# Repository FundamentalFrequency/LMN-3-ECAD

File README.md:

# LMN-3-ECAD

This repository contains the [KiCad 6](https://www.kicad.org/) project files for the LMN-3 PCB.

If you would like to support the project, please consider becoming a [sponsor](https://github.com/sponsors/stonepreston).

## Bill of Materials
| Description                | Model                            | Quantity | URL                                                                                            |
|----------------------------|----------------------------------|----------|------------------------------------------------------------------------------------------------|
| Diode                      | 1N4148                           | 49       | https://www.amazon.com/McIgIcM-1n4148-switching-Standard-Through/dp/B06XB1R2NK                 |
| Rotary Encoder             | EC11                             | 4        | https://www.amazon.com/WayinTop-Encoder-Potentiometer-Electronics-Projects/dp/B08728K3YB?psc=1 |
| Switch                     | 5 pin mechanical keyboard switch | 45       |                                                                                                |
| Joystick                   | COM-09032                        | 1        | https://www.sparkfun.com/products/9032                                                         |                                                                                        |
| Microcontroller            | Teensy 4.1                       | 1        | https://www.pjrc.com/store/teensy41.html                                                       |
| Arduino Header Strip                    |                            | 2      | https://www.amazon.com/gp/product/B07PKKY8BX?psc=1                 |

## Gerbers
Gerber files are available [here](https://github.com/FundamentalFrequency/LMN-3-ECAD/releases) if you would like to have a board house manufacture the PCB. 

## Thanks
This project would not be possible without the following free and open source projects:
- [KiCad](https://www.kicad.org/)
- [Keyswitch Kicad Library](https://github.com/perigoso/keyswitch-kicad-library)

### Sources for Footprints, Symbols, 3-D Models, and Other Resources
#### Encoders (Alps EC11E09244AQ)
- [Product Page](https://www.mouser.com/ProductDetail/Alps-Alpine/EC11E09244AQ?qs=fMKjfF2mFohVUA4%2Ftyw7NQ%3D%3D)
- [Datasheet and Mechanical Drawing](https://tech.alpsalpine.com/prod/e/html/encoder/incremental/ec11/ec11e09244aq.html)
- [3-D Model](https://www.snapeda.com/parts/EC11E09244AQ/ALPS/view-part/?welcome=home&t=EC11E)

#### Teensy 4.1
- [Product Page](https://www.pjrc.com/store/teensy41.html)
- [3-D Model](https://www.snapeda.com/parts/DEV-16771/SparkFun%20Electronics/view-part/?t=teensy)

#### Thumbstick (SparkFun COM-09032)
- [Product Page](https://www.digikey.com/en/products/detail/sparkfun-electronics/COM-09032/6823623)
- [Datasheet](https://media.digikey.com/pdf/Data%20Sheets/Sparkfun%20PDFs/COM-09032_Web.pdf)
- [3-D Model](https://www.snapeda.com/parts/COM-09032/SparkFun%20Electronics/view-part/?t=joystick)
- [Eagle Library](https://github.com/sparkfun/SparkFun-Eagle-Libraries)

#### Keyboard Switches (Keyswitch Kicad Library)
- [Footprints, Symbols, and 3-D Models](https://github.com/perigoso/keyswitch-kicad-library)

## License
Licensed under the  [CC-by-SA 4.0](https://creativecommons.org/licenses/by-sa/4.0/) license.

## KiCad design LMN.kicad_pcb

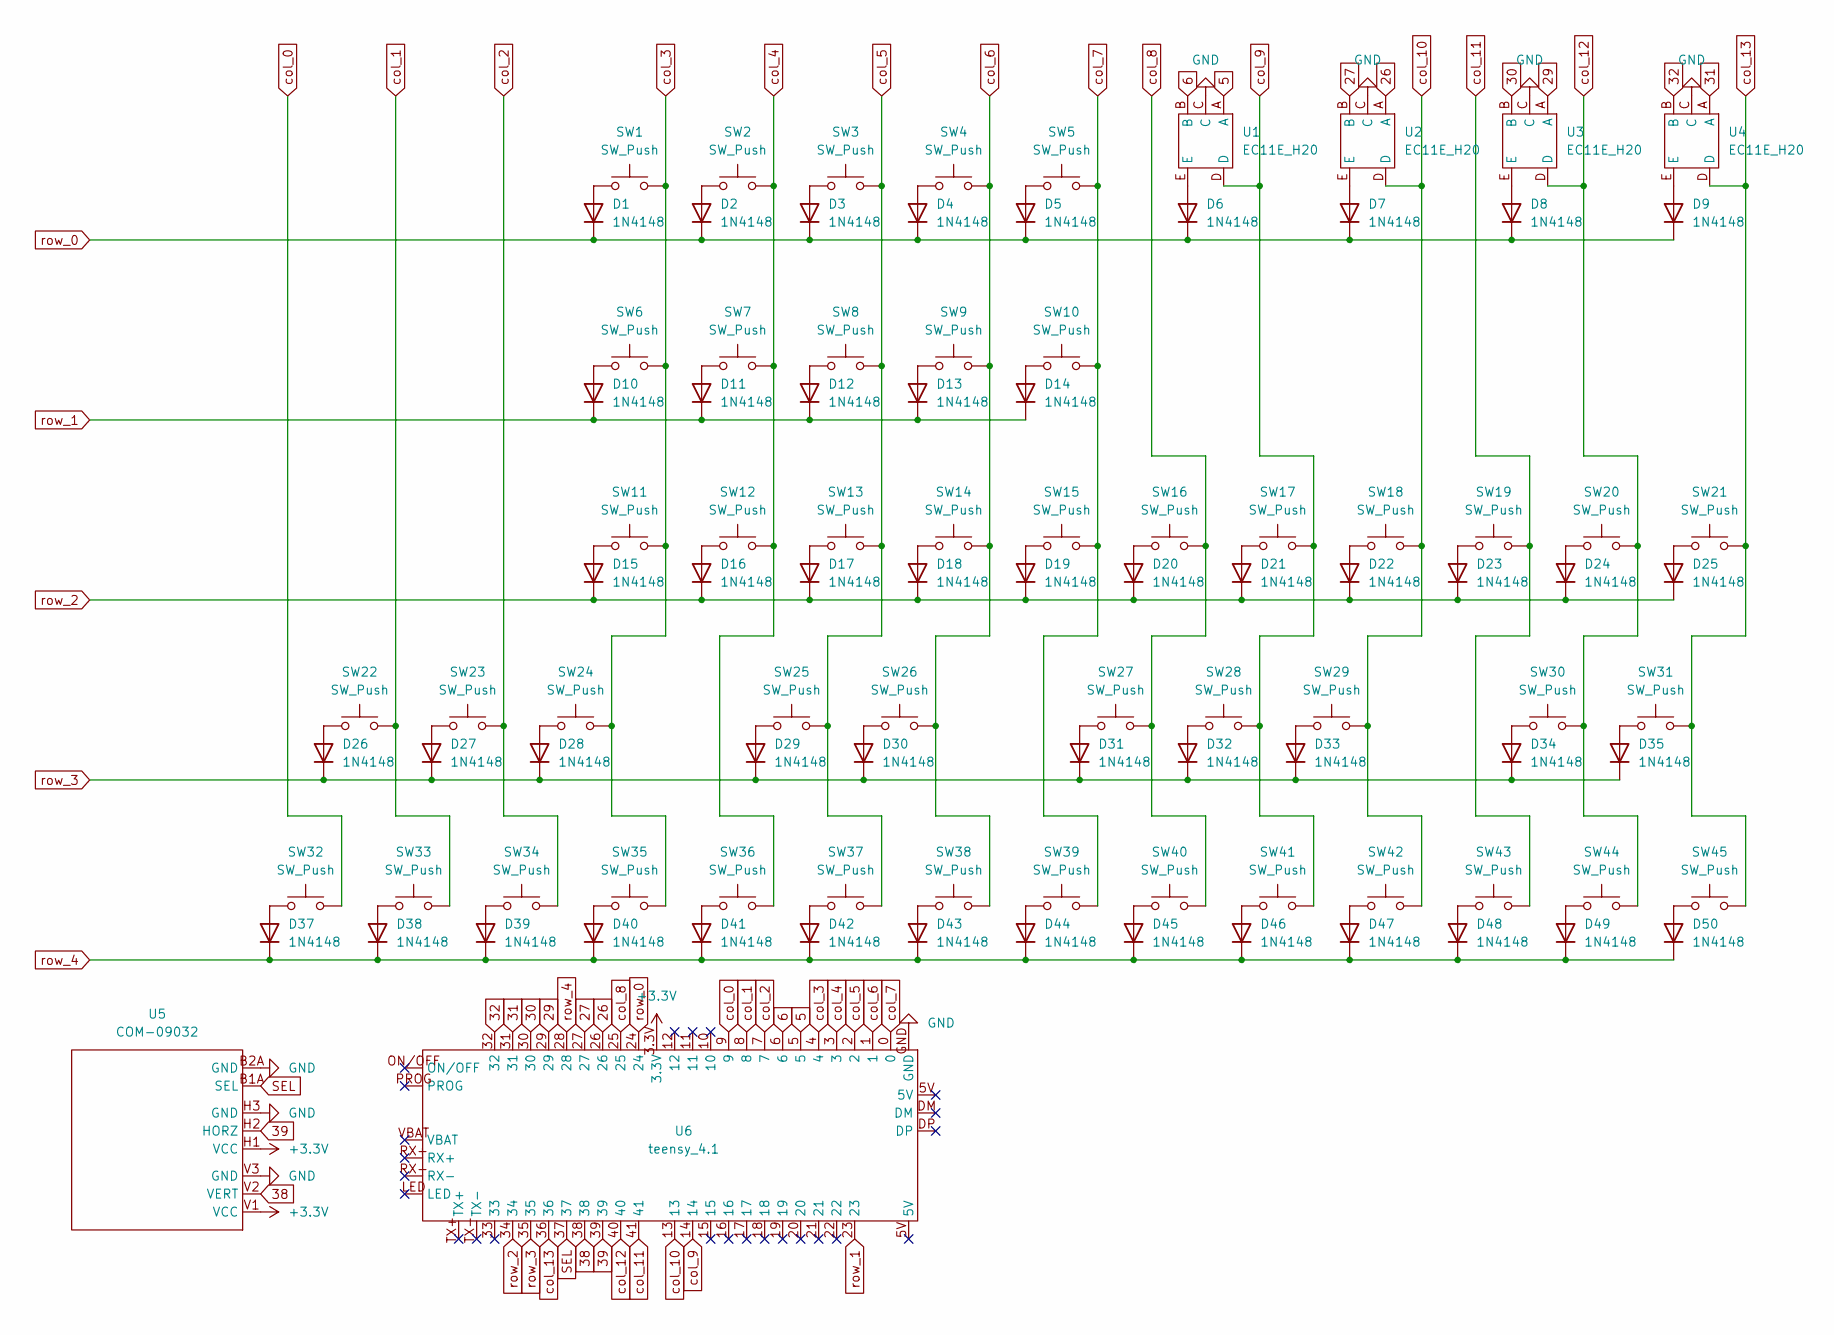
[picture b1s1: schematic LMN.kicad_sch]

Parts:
D1, D2, D3, D4, D5, D6, D7, D8, D9, D10, D11, D12, D13, D14, D15, D16, D17, D18, D19, D20, D21, D22, D23, D24, D25, D26, D27, D28, D29, D30, D31, D32, D33, D34, D35, D37, D38, D39, D40, D41, D42, D43, D44, D45, D46, D47, D48, D49, D50: 1N4148; D_DO-35_SOD27_P7.62mm_Horizontal
SW1, SW2, SW3, SW4, SW5, SW6, SW7, SW8, SW9, SW10, SW11, SW12, SW13, SW14, SW15, SW16, SW17, SW18, SW19, SW20, SW21, SW22, SW23, SW24, SW25, SW26, SW27, SW28, SW29, SW30, SW31, SW32, SW33, SW34, SW35, SW36, SW37, SW38, SW39, SW40, SW41, SW42, SW43, SW44, SW45: SW_Push; SW_Cherry_MX_PCB_1.00u
U1, U2, U3, U4: EC11E_H20
U5: COM-09032
U6: teensy_4.1

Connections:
5: U1.A, U6.5
6: U1.B, U6.6
26: U2.A, U6.26
27: U2.B, U6.27
29: U3.A, U6.29
30: U3.B, U6.30
31: U4.A, U6.31
32: U4.B, U6.32
38: U5.V2 (VERT), U6.38
39: U5.H2 (HORZ), U6.39
+3V3: U5.H1 (VCC), U5.V1 (VCC), U6.3.3V
GND: U1.C, U2.C, U3.C, U4.C, U5.B2A (GND), U5.H3 (GND), U5.V3 (GND), U6.GND
unnamed: D1.2 (A), SW1.1
unnamed: D2.2 (A), SW2.1
unnamed: D3.2 (A), SW3.1
unnamed: D4.2 (A), SW4.1
unnamed: D5.2 (A), SW5.1
unnamed: D6.2 (A), U1.E
unnamed: D7.2 (A), U2.E
unnamed: D8.2 (A), U3.E
unnamed: D9.2 (A), U4.E
unnamed: D10.2 (A), SW6.1
unnamed: D11.2 (A), SW7.1
unnamed: D12.2 (A), SW8.1
unnamed: D13.2 (A), SW9.1
unnamed: D14.2 (A), SW10.1
unnamed: D15.2 (A), SW11.1
unnamed: D16.2 (A), SW12.1
unnamed: D17.2 (A), SW13.1
unnamed: D18.2 (A), SW14.1
unnamed: D19.2 (A), SW15.1
unnamed: D20.2 (A), SW16.1
unnamed: D21.2 (A), SW17.1
unnamed: D22.2 (A), SW18.1
unnamed: D23.2 (A), SW19.1
unnamed: D24.2 (A), SW20.1
unnamed: D25.2 (A), SW21.1
unnamed: D26.2 (A), SW22.1
unnamed: D27.2 (A), SW23.1
unnamed: D28.2 (A), SW24.1
unnamed: D29.2 (A), SW25.1
unnamed: D30.2 (A), SW26.1
unnamed: D31.2 (A), SW27.1
unnamed: D32.2 (A), SW28.1
unnamed: D33.2 (A), SW29.1
unnamed: D34.2 (A), SW30.1
unnamed: D35.2 (A), SW31.1
unnamed: D37.2 (A), SW32.1
unnamed: D38.2 (A), SW33.1
unnamed: D39.2 (A), SW34.1
unnamed: D40.2 (A), SW35.1
unnamed: D41.2 (A), SW36.1
unnamed: D42.2 (A), SW37.1
unnamed: D43.2 (A), SW38.1
unnamed: D44.2 (A), SW39.1
unnamed: D45.2 (A), SW40.1
unnamed: D46.2 (A), SW41.1
unnamed: D47.2 (A), SW42.1
unnamed: D48.2 (A), SW43.1
unnamed: D49.2 (A), SW44.1
unnamed: D50.2 (A), SW45.1
SEL: U5.B1A (SEL), U6.37
col_0: SW32.2, U6.9
col_1: SW22.2, SW33.2, U6.8
col_2: SW23.2, SW34.2, U6.7
col_3: SW1.2, SW6.2, SW11.2, SW24.2, SW35.2, U6.4
col_4: SW2.2, SW7.2, SW12.2, SW36.2, U6.3
col_5: SW3.2, SW8.2, SW13.2, SW25.2, SW37.2, U6.2
col_6: SW4.2, SW9.2, SW14.2, SW26.2, SW38.2, U6.1
col_7: SW5.2, SW10.2, SW15.2, SW39.2, U6.0
col_8: SW16.2, SW27.2, SW40.2, U6.25
col_9: SW17.2, SW28.2, SW41.2, U1.D, U6.14
col_10: SW18.2, SW29.2, SW42.2, U2.D, U6.13
col_11: SW19.2, SW43.2, U6.41
col_12: SW20.2, SW30.2, SW44.2, U3.D, U6.40
col_13: SW21.2, SW31.2, SW45.2, U4.D, U6.36
row_0: D1.1 (K), D2.1 (K), D3.1 (K), D4.1 (K), D5.1 (K), D6.1 (K), D7.1 (K), D8.1 (K), D9.1 (K), U6.24
row_1: D10.1 (K), D11.1 (K), D12.1 (K), D13.1 (K), D14.1 (K), U6.23
row_2: D15.1 (K), D16.1 (K), D17.1 (K), D18.1 (K), D19.1 (K), D20.1 (K), D21.1 (K), D22.1 (K), D23.1 (K), D24.1 (K), D25.1 (K), U6.34
row_3: D26.1 (K), D27.1 (K), D28.1 (K), D29.1 (K), D30.1 (K), D31.1 (K), D32.1 (K), D33.1 (K), D34.1 (K), D35.1 (K), U6.35
row_4: D37.1 (K), D38.1 (K), D39.1 (K), D40.1 (K), D41.1 (K), D42.1 (K), D43.1 (K), D44.1 (K), D45.1 (K), D46.1 (K), D47.1 (K), D48.1 (K), D49.1 (K), D50.1 (K), U6.28

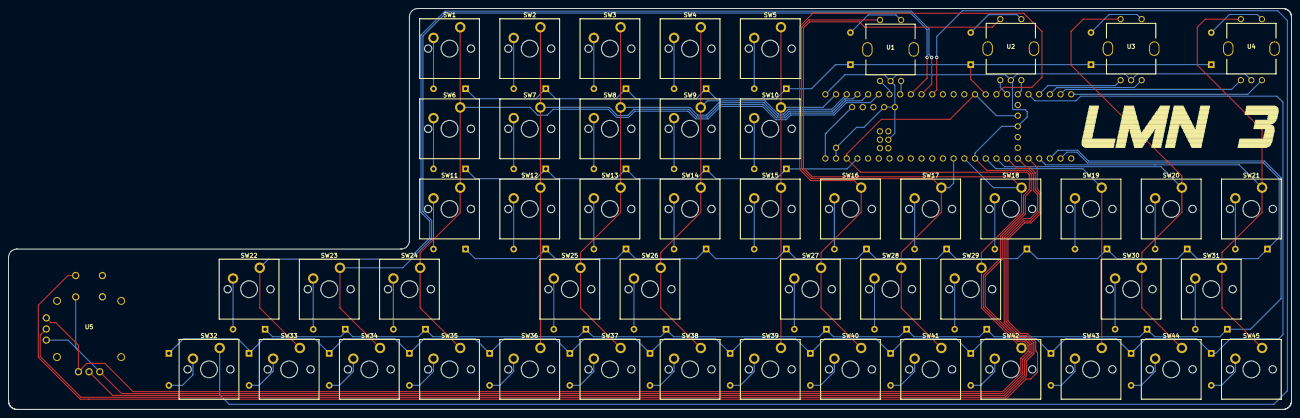
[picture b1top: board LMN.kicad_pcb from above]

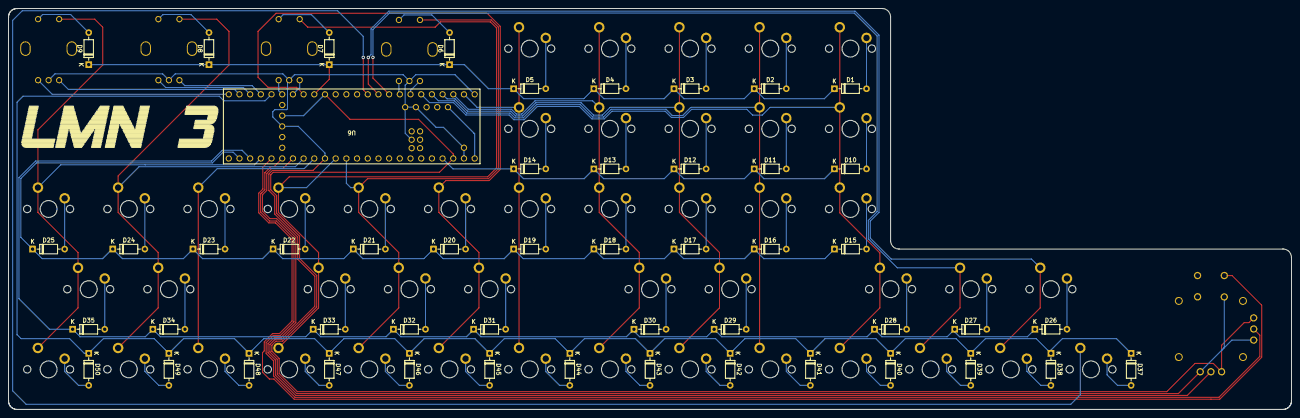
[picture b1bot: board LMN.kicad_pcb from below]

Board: 2 copper layers, 304.8 x 95.2 mm, 100 parts (50 on the bottom side), 81 nets.

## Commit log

2022-02-22 Change logos and other graphics
2022-02-23 Add mounting holes
2022-02-24 Update gerbers, fix incorrect footprint in switch
2022-02-24 Update gerbers
2022-04-26 Add README
2022-04-27 Add README, remove old models
2022-05-13 Remove gerbers from source
2022-05-13 Rename LICENSE.md to LICENSE
